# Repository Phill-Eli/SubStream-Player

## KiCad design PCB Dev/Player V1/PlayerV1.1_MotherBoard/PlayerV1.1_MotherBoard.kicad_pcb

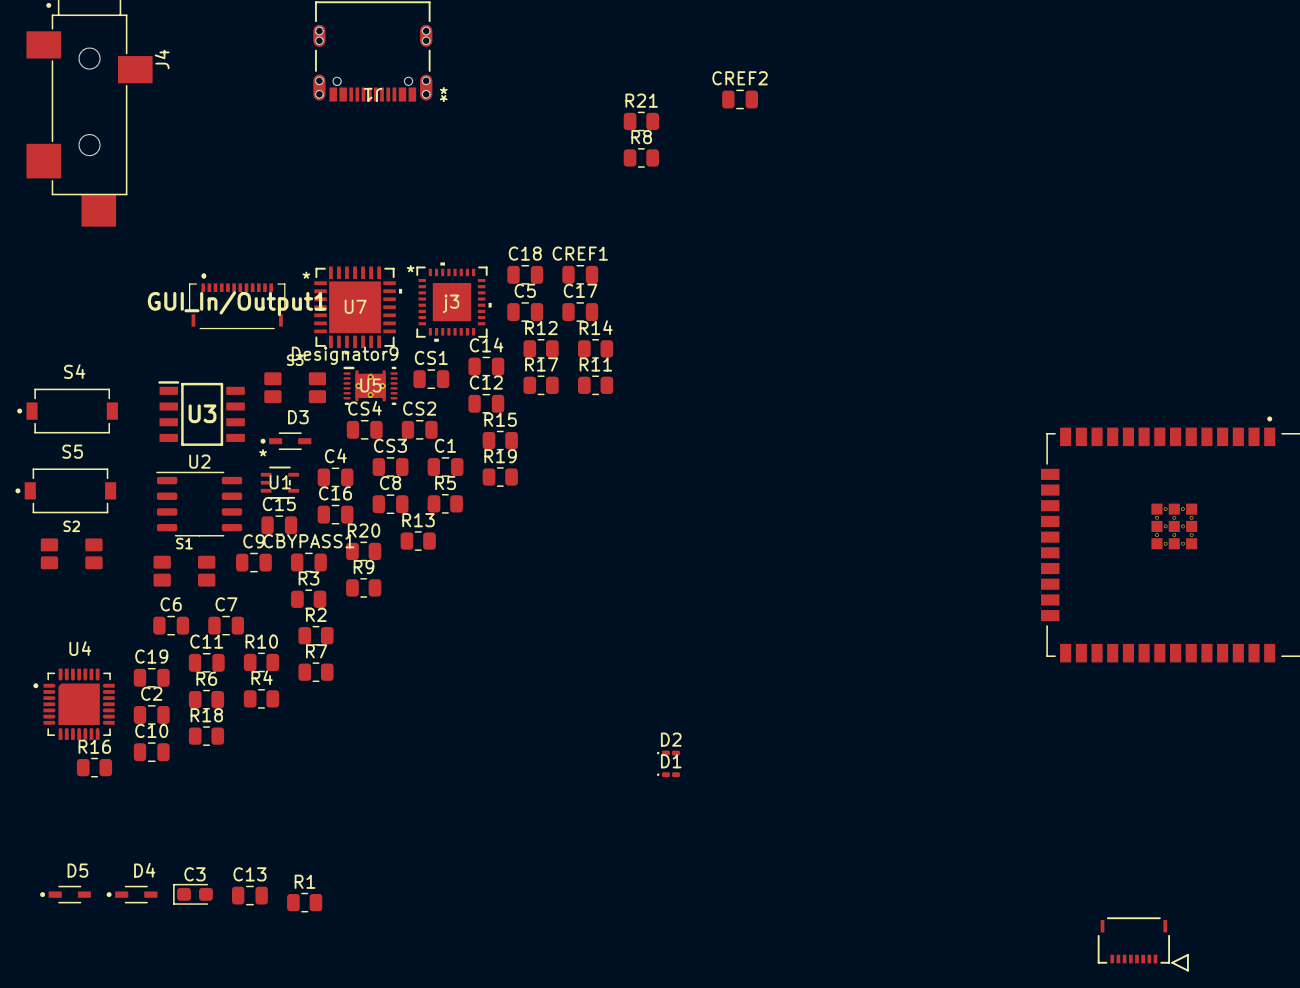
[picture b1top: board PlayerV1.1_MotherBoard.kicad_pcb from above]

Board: 2 copper layers, 69 parts (0 on the bottom side), 51 nets, no tracks yet.

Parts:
C1, C6: 10uF; C_0805_2012Metric
C2, C7: 470uF; C_0805_2012Metric
C3: 10uF; CP_EIA-2012-15_AVX-P
C4, C8, C16: 1uF; C_0805_2012Metric
C5, C10, C12, C17, C18: 100nF; C_0805_2012Metric
C9: 22uF; C_0805_2012Metric
C11: 470nF; C_0805_2012Metric
C13: 4.7uF; C_0805_2012Metric
C14, C19: 2.2uF; C_0805_2012Metric
C15: 0.1uF; C_0805_2012Metric
CBYPASS1: 2.2uF; C_0805_2012Metric
CREF1: 10uF; C_0805_2012Metric
CREF2: 0.1uF; C_0805_2012Metric
CS1, CS4: 1uF; C_0805_2012Metric
CS2: 10uF; C_0805_2012Metric
CS3: 0.1uF; C_0805_2012Metric
Cell_Input1: 5034800800; ul_5034800800
D1, D2: LED; LED_0201_0603Metric_Pad0.64x0.40mm_HandSolder
D3, D4, D5: CDSOD323-T05LC; SOD2513X114N
GUI_In/Output1: 503480-1200; 5034801200
J1: USB_C_Receptacle_USB2.0; 12402012E212A_AMP
J4: SJ-3524-SMT-BE; CUI_SJ-3524-SMT-BE
R1, R3: 1k; R_0805_2012Metric
R2: 0.4; R_0805_2012Metric
R4, R5: 5.1K; R_0805_2012Metric
R6: 100K; R_0805_2012Metric
R7: 2k; R_0805_2012Metric
R8: 22.1K; R_0805_2012Metric
R9: 47.5K; R_0805_2012Metric
R10: 1K; R_0805_2012Metric
R11, R12, R13, R15, R16, R17, R18, R21: 10K; R_0805_2012Metric
R14: 0.01; R_0805_2012Metric
R19, R20: 4.7K; R_0805_2012Metric
S1, S2, S3: EVQ-P7B01P
S4, S5: PTS636; SW_PTS636_SM43J_SMTR_LFS
U1: MIC5213-2.5YC5-TR; SC-70_C5_MCH
U2: TP4056; SOP-8_3.9x4.9mm_P1.27mm
U3: AP7217A; SOIC127P600X175-8N
U4: CP2102N-A02-GQFN28R; IC_CP2102N-A02-GQFN28R
U5: BQ27441DRZR-G1A; Copy of DRZ0012A
U6: ESP32-WROOM-32E_(16MB); XCVR_ESP32-WROOM-32E_(16MB)
U7: MCP23017-E/ML; QFN28_6x6MC_MCH
j3: LM49450SQ_NOPB; SQA32A

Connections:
+BATT: C2.2, C4.2, C6.2, C8.2, R6.2, R14.1, R14.2, U1.1 (EN), U1.5 (IN), U2.5 (BAT), U5.6 (BAT), U5.7 (SRN), U5.8 (SRP)
/BCLK: U6.12 (IO27), j3.7 (I2S_CLK)
/D+: D5.1, J1.A6 (D+), J1.B6 (D+), U4.4 (D+)
/D-: D4.1, J1.A7 (D-), J1.B7 (D-), U4.5 (D-)
/DOUT: U6.10 (IO25), j3.6 (I2S_SDI)
/DTR: R15.2, U4.28 (DTR)
/EN: C17.2, R21.2, S4.1
/HPL: J4.2, j3.29 (HPL)
/HPR: J4.3, j3.27 (HPR)
/HPS: J4.4, j3.26 (HPS)
/HPVDD: C7.2, CS1.2, U1.4 (OUT), j3.28 (HPVDD)
/HPVSS: C16.2, j3.30 (HPVSS)
/I2S_WS: U6.11 (IO26), j3.5 (I2S_WS)
/IO0_BTN: C18.2, S5.1, U6.25 (IO0)
/MCLK: U6.35 (TXD0), j3.8 (MCLK)
/PWR_BTN: S1.1, S1.1', U6.24 (IO2)
/RTS: R16.1, U4.24 (RTS)
/RXD: R17.2, U4.25 (RXD)
/RXD0: R18.1, U6.27 (IO16)
/SCL: R19.2, U5.2 (SCL), U6.36 (IO22), U7.8 (SCL), j3.9 (SCL)
/SDA: R20.2, U5.1 (SDA), U6.33 (IO21), U7.9 (SDA), j3.3 (SDA)
/TXD: R18.2, U4.26 (TXD)
/TXD0: R17.1, U6.28 (IO17)
/V+_BTN: S2.1, S2.1', U7.21 (GPA4)
/V-_BTN: S3.1, S3.1', U7.22 (GPA5)
/VCLK: Cell_Input1.5, U6.30 (IO18)
/VCS: Cell_Input1.6, U6.29 (IO5)
/VMISO: Cell_Input1.4, U6.31 (IO19)
/VMOSI: Cell_Input1.3, U6.37 (IO23)
GND: C1.1, C2.1, C3.1, C4.1, C5.1, C6.1, C7.1, C8.1, C9.1, C10.1, C11.1, C12.1, C13.1, C14.1, C15.1, C16.1, C17.1, C18.1, CBYPASS1.1, CREF1.1, CREF2.1, CS1.1, CS2.1, CS3.1, CS4.1, Cell_Input1.2, Cell_Input1.7, D3.2, D4.2, D5.2, GUI_In/Output1.11, J4.1, R4.1, R5.1, R7.1, R9.1, R11.2, R13.1, S1.2, S1.2', S2.2, S2.2', S3.2, S3.2', S4.2, S5.2, U1.3 (GND), U2.3 (GND), U4.3 (GND), U4.29 (EXP), U5.3 (VSS), U5.13 (PAD), U6.1 (GND), U6.15 (GND), U6.38 (GND), U6.39_1 (GND), U6.39_2 (GND), U6.39_3 (GND), U6.39_4 (GND), U6.39_5 (GND), U6.39_6 (GND), U6.39_7 (GND), U6.39_8 (GND), U6.39_9 (GND), U7.6 (VSS), U7.11 (A0), U7.12 (A1), U7.13 (A2), U7.29 (HTAB), j3.2 (CPGND), j3.4 (DGND), j3.12 (GND), j3.21 (LSGND), j3.25 (HPGND), j3.33 (DAP)
unnamed: C1.2, D1.2 (A), D2.2 (A), R2.2, U2.4 (VCC), U2.8 (CE)
unnamed: C11.2, U5.5 (VDD)
unnamed: C19.1, j3.31 (C1N)
unnamed: C19.2, j3.1 (C1P)
unnamed: CBYPASS1.2, j3.17 (BYPASS)
unnamed: CREF1.2, CREF2.2, j3.13 (REF)
unnamed: CS4.2, j3.32 (CPVDD)
unnamed: D1.1 (K), R1.1
unnamed: D2.1 (K), R3.1
unnamed: J1.A5 (CC1), R5.2
unnamed: J1.B5 (CC2), R4.2
unnamed: R1.2, U2.6 (STDBY)
unnamed: R3.2, U2.7 (CHRG)
unnamed: R7.2, U2.2 (PROG)
unnamed: R8.1, R9.2, U4.7 (VREGIN), U4.8 (VBUS)
unnamed: R10.1, U4.9 (~RST)
unnamed: R11.1, U5.10 (BIN)
unnamed: R12.1, U5.12 (GPOUT)
unnamed: R13.2, U4.11 (~SUSPEND)
VBUS: C5.2, D3.1, R8.2
VCC: C3.2, C9.2, C10.2, C12.2, C13.2, C14.2, C15.2, CS2.2, CS3.2, Cell_Input1.1, Cell_Input1.8, GUI_In/Output1.12, R2.1, R10.2, R12.2, R19.1, R20.1, R21.1, U4.6 (VDD), U6.2 (3V3), U6.3 (EN), U7.5 (VDD), U7.14 (*RESET), j3.10 (DVDD), j3.11 (IOVDD), j3.16 (VDD), j3.18 (LSVDD), j3.24 (LSVDD)

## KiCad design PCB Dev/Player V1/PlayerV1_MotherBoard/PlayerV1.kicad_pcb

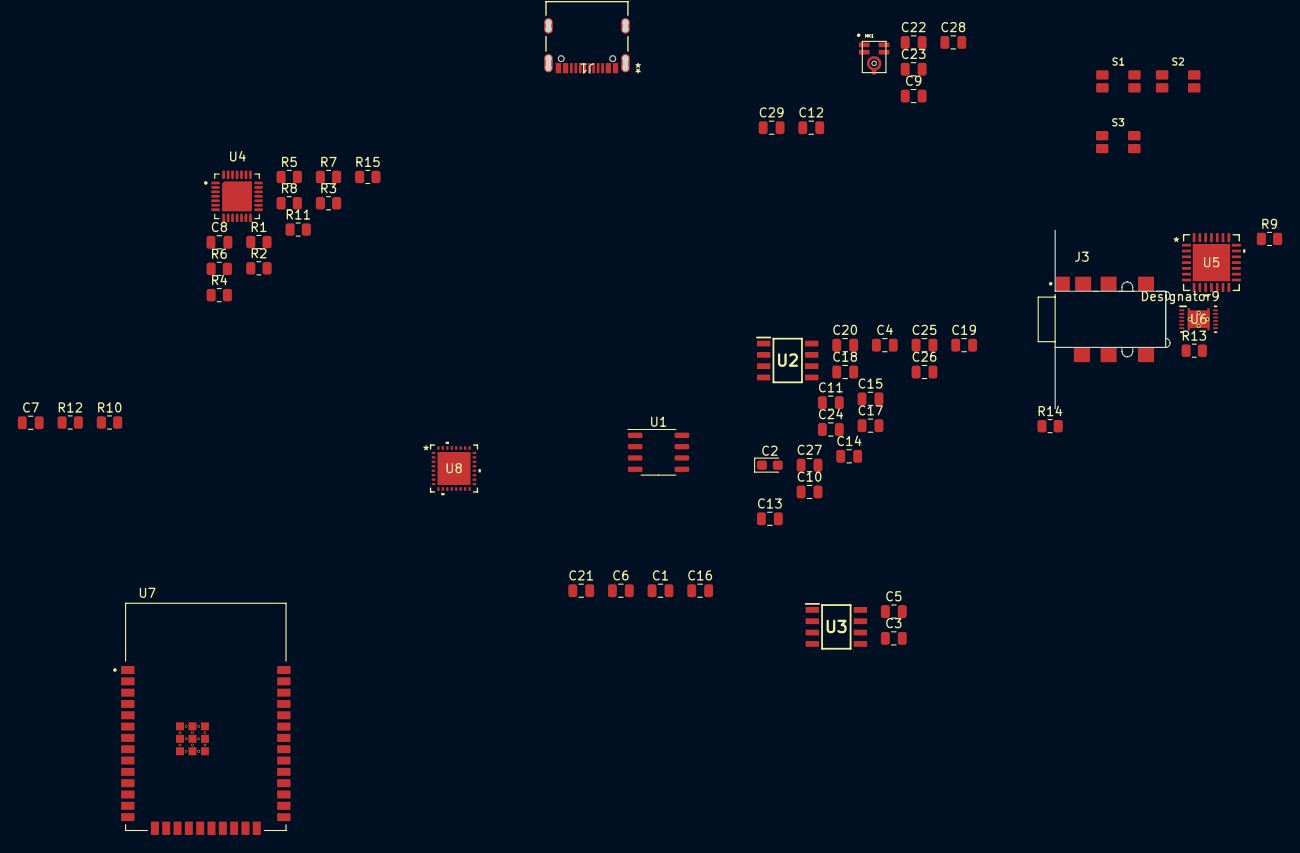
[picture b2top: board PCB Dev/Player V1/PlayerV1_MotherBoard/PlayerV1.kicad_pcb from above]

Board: 2 copper layers, 58 parts (0 on the bottom side), 41 nets, no tracks yet.

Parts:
C1, C6, C16, C28, C29: 10uF; C_0805_2012Metric
C2: 10uF; CP_EIA-2012-15_AVX-P
C3, C4, C5, C9, C10, C11, C12, C13, C14, C15, C24, C25, C26, C27: 1uF; C_0805_2012Metric
C7: 100nF; C_0805_2012Metric
C8: 4.7uF; C_0805_2012Metric
C17, C20, C22, C23: 0.1uF; C_0805_2012Metric
C18, C19, C21: 2.2uF; C_0805_2012Metric
J1: USB_C_Receptacle_USB2.0; 12402012E212A_AMP
J3: SJ-43615TS-SMT; CUI_SJ-43615TS-SMT
MK1: ICS-40618; MIC_ICS-40618
R1, R3: 1k; R_0805_2012Metric
R2: 0.4; R_0805_2012Metric
R4: 2k; R_0805_2012Metric
R5, R6, R15: 100K; R_0805_2012Metric
R7: 22.1K; R_0805_2012Metric
R8: 47.5K; R_0805_2012Metric
R9: 1K; R_0805_2012Metric
R10, R11, R12, R13, R14: 10K; R_0805_2012Metric
S1, S2, S3: EVQ-P7B01P
U1: TP4056; SOP-8_3.9x4.9mm_P1.27mm
U2, U3: AP7217A; SOIC127P600X175-8N
U4: CP2102N-A02-GQFN28R; IC_CP2102N-A02-GQFN28R
U5: MCP23017-E/ML; QFN28_6x6MC_MCH
U6: BQ27441DRZR-G1A; Copy of DRZ0012A
U7: ESP32-WROOM-32E_(16MB); XCVR_ESP32-WROOM-32E_(16MB)
U8: AK4619VN; AK4619VN_AKM

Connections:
+BATT: C4.2, C5.2, C6.2, R5.2, R6.2, U1.5 (BAT), U2.4 (Vin), U2.8 (EN), U3.4 (Vin), U3.8 (EN)
/AOUT1L: C27.1, U8.22 (AOUT1L)
/AOUT1R: C26.1, U8.23 (AOUT1R)
/AOUT2L: C25.1, U8.24 (AOUT2L)
/AOUT2R: C24.1, U8.25 (AOUT2R)
/AVDRV: C18.2, U8.5 (AVDRV)
/D+: J1.A6 (D+), J1.B6 (D+), U4.4 (D+)
/D-: J1.A7 (D-), J1.B7 (D-), U4.5 (D-)
/DTR: R11.2, U4.28 (DTR)
/IN1N: C13.1, U8.15 (IN1N/AIN2L/GND3L)
/IN1P: C12.1, U8.16 (IN1P/AIN1L/AIN3L)
/IN2N: C15.1, U8.13 (IN2N/AIN2R/GND3R)
/IN2P: C14.1, U8.14 (IN2P/AIN1R/AIN3R)
/IN3N: C11.1, U8.11 (IN3N/AIN5L/GND6L)
/IN3P: C10.1, U8.12 (IN3P/AIN4L/AIN6L)
/LRCK: U7.11 (IO26), U8.6 (LRCK)
/MCLK: U7.35 (TXD0), U8.8 (MCLK)
/PDN: U7.26 (IO4), U8.26 (PDN)
/RTS: R12.1, U4.24 (RTS)
/RXD: R13.2, U4.25 (RXD)
/RXD0: R14.1, U7.27 (IO16)
/SCL: U7.36 (IO22), U8.28 (SCL/SCLK)
/SDA: U7.33 (IO21), U8.30 (SDA/SO)
/TVDD: C16.1, C17.2, U8.3 (TVDD)
/TXD: R14.2, U4.26 (TXD)
/TXD0: R13.1, U7.28 (IO17)
/VCOM: C21.2, U8.17 (VCOM)
GND: C1.1, C2.1, C2.2, C3.1, C4.1, C5.1, C6.1, C7.1, C7.2, C8.1, C8.2, C9.1, C13.2, C15.2, C16.2, C17.1, C18.1, C19.1, C19.2, C20.1, C20.2, C21.1, C22.1, C22.2, C23.1, C23.2, C28.1, C28.2, C29.1, C29.2, MK1.3 (GND), MK1.4 (GND), MK1.5 (VDD), R2.1, R4.1, R8.1, R9.2, R10.1, R15.1, U1.3 (GND), U2.1 (GND), U2.2 (VRo), U2.3 (GND), U2.5 (GND), U2.7 (GND), U3.1 (GND), U3.3 (GND), U3.5 (GND), U3.7 (GND), U4.3 (GND), U4.6 (VDD), U4.29 (EXP), U7.1 (GND), U7.2 (3V3), U7.15 (GND), U7.38 (GND), U7.39_1 (GND), U7.39_2 (GND), U7.39_3 (GND), U7.39_4 (GND), U7.39_5 (GND), U7.39_6 (GND), U7.39_7 (GND), U7.39_8 (GND), U7.39_9 (GND), U8.2 (SDIN2), U8.4 (VSS2), U8.18 (AVDD), U8.19 (VSS1), U8.20 (VREFL), U8.21 (VREFH)
unnamed: C1.2, R2.2, U1.4 (VCC), U1.8 (CE)
unnamed: C9.2, R15.2, U7.3 (EN)
unnamed: C10.2, MK1.1 (OUTPUT+)
unnamed: C11.2, MK1.2 (OUTPUT-)
unnamed: R1.2, U1.6 (STDBY)
unnamed: R3.2, U1.7 (CHRG)
unnamed: R4.2, U1.2 (PROG)
unnamed: R5.1, U2.6 (VDo)
unnamed: R6.1, U3.6 (VDo)
unnamed: R7.1, R8.2, U4.8 (VBUS)
unnamed: R10.2, U4.11 (~SUSPEND)
unnamed: R9.1, U4.7 (VREGIN), U4.9 (~RST)
VDC: C3.2, U3.2 (VRo)

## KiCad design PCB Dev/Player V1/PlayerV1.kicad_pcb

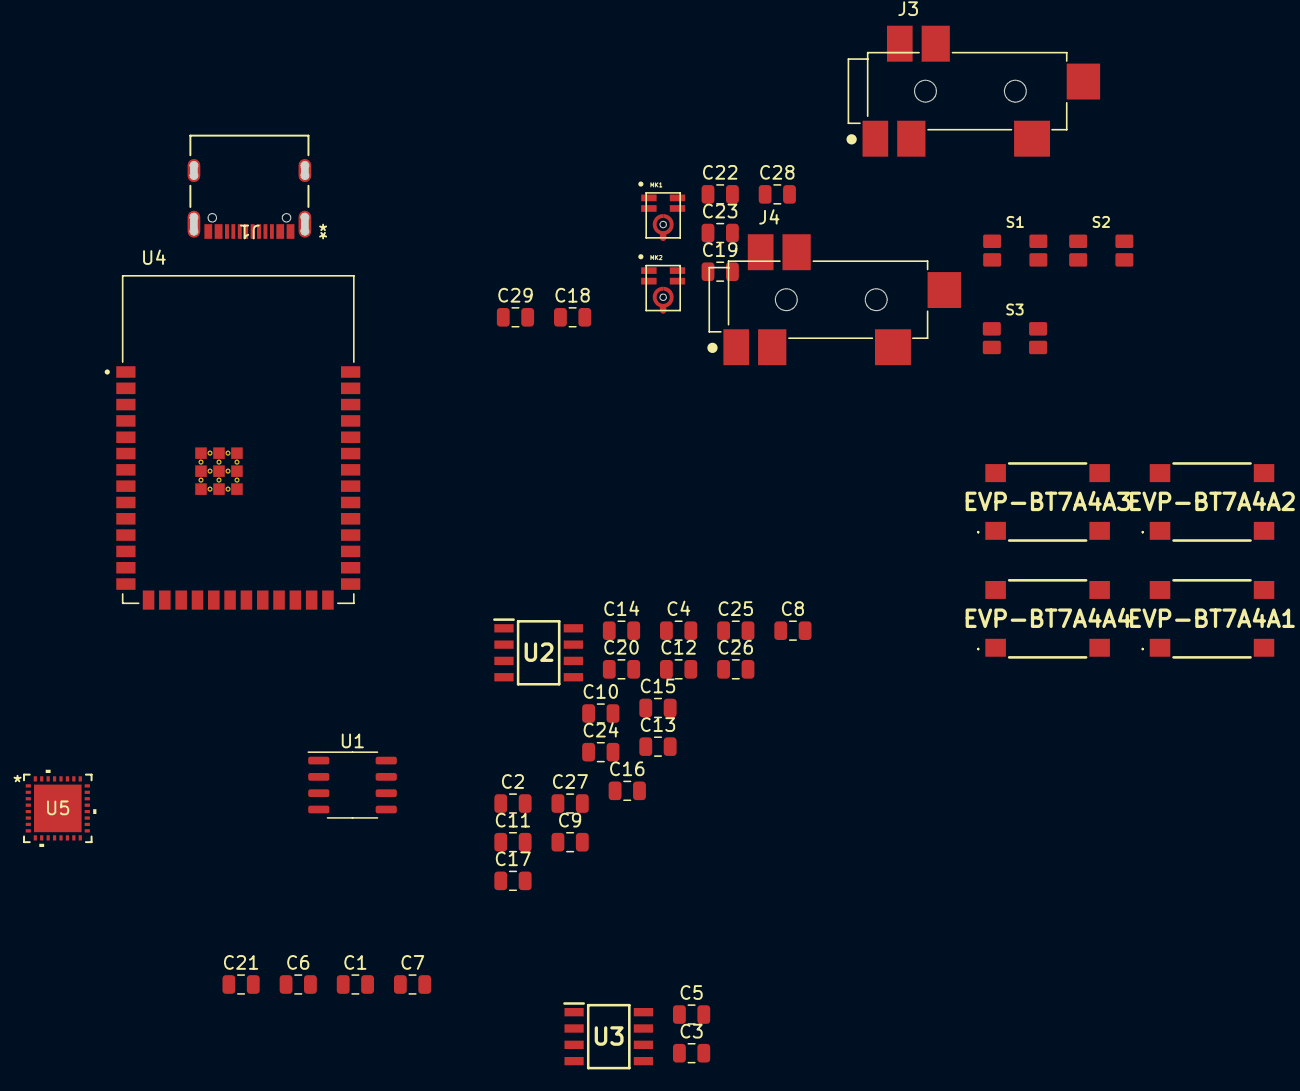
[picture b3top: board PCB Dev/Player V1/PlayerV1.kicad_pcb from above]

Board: 2 copper layers, 46 parts (0 on the bottom side), 26 nets, no tracks yet.

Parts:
C1, C6, C7, C28, C29: 10uF; C_0805_2012Metric
C2, C3, C4, C5, C9, C10, C11, C12, C15, C16, C17, C18, C19, C24, C25, C26, C27: 1uF; C_0805_2012Metric
C8, C20, C21: 2.2uF; C_0805_2012Metric
C13, C14, C22, C23: 0.1uF; C_0805_2012Metric
EVP-BT7A4A1, EVP-BT7A4A2, EVP-BT7A4A3, EVP-BT7A4A4: EVP-BT7A4A000; EVPBT7A4A000
J1: USB_C_Receptacle_USB2.0; 12402012E212A_AMP
J3, J4: SJ-43516-SMT-U; CUI_SJ-43516-SMT-GR
MK1, MK2: ICS-40618; MIC_ICS-40618
S1, S2, S3: EVQ-P7B01P
U1: TP4056; SOP-8_3.9x4.9mm_P1.27mm
U2, U3: AP7217A; SOIC127P600X175-8N
U4: ESP32-S3-WROOM-1-N8; XCVR_ESP32S3WROOM1N8R8
U5: AK4619VN; AK4619VN_AKM

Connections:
+BATT: C4.2, C5.2, C6.2, U1.5 (BAT), U2.4 (Vin), U2.8 (EN), U3.4 (Vin), U3.8 (EN)
/AOUT1L: C27.1, U5.22 (AOUT1L)
/AOUT1R: C26.1, U5.23 (AOUT1R)
/AOUT2L: C25.1, U5.24 (AOUT2L)
/AOUT2R: C24.1, U5.25 (AOUT2R)
/AVDRV: C20.2, U5.5 (AVDRV)
/IN1N: C17.1, U5.15 (IN1N/AIN2L/GND3L)
/IN1P: C18.1, U5.16 (IN1P/AIN1L/AIN3L)
/IN2N: C15.1, U5.13 (IN2N/AIN2R/GND3R)
/IN2P: C16.1, U5.14 (IN2P/AIN1R/AIN3R)
/IN3N: C10.1, U5.11 (IN3N/AIN5L/GND6L)
/IN3P: C9.1, U5.12 (IN3P/AIN4L/AIN6L)
/IN4N: C12.1, U5.9 (IN4N/AIN5R/GND6R)
/IN4P: C11.1, U5.10 (IN4P/AIN4R/AIN6R)
/SCL: U4.17 (IO9), U5.28 (SCL/SCLK)
/SDA: U4.12 (IO8), U5.30 (SDA/SO)
/TVDD: C7.1, C13.2, U5.3 (TVDD)
/VCOM: C21.2, U5.17 (VCOM)
GND: C1.1, C2.1, C2.2, C3.1, C4.1, C5.1, C6.1, C7.2, C8.1, C8.2, C13.1, C14.1, C14.2, C15.2, C17.2, C19.1, C20.1, C21.1, C22.1, C22.2, C23.1, C23.2, C28.1, C28.2, C29.1, C29.2, MK1.3 (GND), MK1.4 (GND), MK1.5 (VDD), MK2.3 (GND), MK2.4 (GND), MK2.5 (VDD), U1.3 (GND), U2.1 (GND), U2.2 (VRo), U2.3 (GND), U2.5 (GND), U2.7 (GND), U3.1 (GND), U3.3 (GND), U3.5 (GND), U3.7 (GND), U4.1 (GND), U4.2 (3V3), U4.40 (GND), U5.2 (SDIN2), U5.4 (VSS2), U5.18 (AVDD), U5.19 (VSS1), U5.20 (VREFL), U5.21 (VREFH)
unnamed: C1.2, U1.4 (VCC), U1.8 (CE)
unnamed: C9.2, MK1.1 (OUTPUT+)
unnamed: C10.2, MK1.2 (OUTPUT-)
unnamed: C11.2, MK2.1 (OUTPUT+)
unnamed: C12.2, MK2.2 (OUTPUT-)
unnamed: C19.2, U4.3 (EN)
VDC: C3.2, U3.2 (VRo)

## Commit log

2023-05-02 AK4619VN
    Added main audio codec chip to to schematic, found out about single ended vs differential inputs and will apply this to the design.
    NOTE* Learn more about how to distance analog and digital signals, and the best practice for making a ground planes of these two.
2023-07-19 Working Players in dev and testing
    Tested a wav player tutorial
    it didn't work so I found other options
    found an esp32 audio master library that simplifies playing audio, it plays both wav and mp3 effortlessly
    when trying to use a 128x64px screen and play audio, audio had a pretty significant delay in its run so I found a fix
    most operational version of code is running on both cores of the esp32, now the display and audio run simultaneously perfectly fine
2023-07-30 lil pcb changes
2023-08-04 L part
2023-08-07 a2dp source functionality
    both a2dp source and sink code works,
    can send data stream(.raw, .wav) to sink devices like headphones and speakers
    Just need to make sure to scan for sinks first so I can acquire the pairing code
    now hardware prototypes can be continued while working on combining the code effectively
2023-08-20 gui, docs
    looked into developing a gui, and added some docs for potential hardware
2023-08-31 PCB Work
    worked on schematic for player
    added voltage regulator and charging circuit
    worked on connections for audio codec
2023-09-12 PCB Dev
    Added headphone jacks amp, and stereo speakers amp
    added gui interface buttons though they may have to be put in another pcb
    learned esp32 s3 does not have bluetooth a2dp so I need to switch to esp32 wroom 32E with 16mb instead only issue is gpio are becoming scarce
2023-09-25 name changed to substream player
    added headphone jack regulator
    added tip ring switch jack
    added tvs diodes on usb2.0 jack
    have the gpio expander sorted
    need to finish the battery gauge connections
    need to add the wire outs for the gui board
2023-09-26 library updates
    imported dxf of pcb
    fixed footprint library
2023-09-26 quick update
    :)
2023-09-26 ?
    ?
2023-10-01 added all jst connectors
    new upward facing jst connectors
    fixed footprint issue on the usbC port that resulted in a malformed board outline
    need to add holes for the usbc port somehow
    need to start laying out the pcb after using the component measurements to make proper pcb heights, cutouts, and tactile buttons
2023-10-14 code
    had to revise the code for the display and the audio so both can operate at the same time
    using dma on both aspects already
    dma on the display fixed it's operation issues
    though dma was already in use on the i2s port and it was still stuttering so I have almost no official idea what the issue actually is
    though, apparently the i2s amp i am currently using may be the issue so well have to make the official prototype then see
    because then i wont have to worry about
2023-10-19 none
2023-11-14 sprites
    learning to use sprites for GUI
2023-11-27 Code Updates
    File explorer is going good
    added a simple button library that enables all sorts of button presses
    setup logic that opens pages pretty well
    have to edit the logic that determines the button function depending on the page displayed
    once I confirm I can play audio and display image ill finalize pcb design and mechanical design
2023-11-30 b
    b
2024-01-04 Edited main GUI folder
2024-02-13 Transferred in Onshape models
    Turn Onshape files into solidworks files, as it is he program I prefer to work in
2024-02-13 idek
